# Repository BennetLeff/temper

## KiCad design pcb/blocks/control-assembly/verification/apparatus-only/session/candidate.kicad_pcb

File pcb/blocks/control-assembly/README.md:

# Control-assembly target context (P3 U1)

Authoritative working context for buck/MCU composition. The production board
(`pcb/temper.kicad_pcb`) is read-only; this directory is the only P3-owned
target description.

## Files

- `target-context.json` — outline, six-layer stackup, domains, reserved
  regions, replacement ledger, provenance digests. R1.
- `interfaces.json` — internal required connections vs future RTD/safety/
  programming obligations. Future endpoints are obligations, not connectors.

## Key facts (measured, not inherited)

- Outline 164x234 mm: rect (8,20)-(172,254), Edge.Cuts gr_poly.
- Six copper layers, physical order F.Cu / In3.Cu / In1.Cu / In2.Cu / In4.Cu /
  B.Cu (outer 0.07 mm, inner 0.035 mm; 1.6 mm total; ENIG). Ordinal IDs
  (0/3/1/2/4/31) are not physical order.
- Buck prototype is two-layer 50x40 mm with J1/J2/TP1-TP4/H1-H4 fixtures.
  Only the functional nine transfer:
  U3 (LMR51430), L2 (5.6 uH SRP1265A), C9 (10 uF in), C10 (100 nF boot),
  C11/C12 (2x22 uF out), C13 (100 nF HF), R16 (100 k), R17 (22.1 k).
- MCU source is ten components: module + c_vcc1/c_vcc2 + r_en/c_en +
  r_boot + btn_reset/btn_boot + 2x I2C pullups.
- Existing placeholders: U27 (ESP32-S3-WROOM-1 at 33.1,47.96 rot 90),
  U3 (117.93,149.08), L2 (135.29,147.93). Reserved envelopes:
  MCU 18-52 x 28-68, antenna keepout 18-52 x 20-32, buck 100-146 x 132-162.

## For P1

Definite outline, stackup, allowed regions, and interface obligations are in
the two JSON files. Every input carries a source path and sha256 in
`target-context.json/provenance`. Pending P1 inputs (combined source
wrapper/export, accepted `pcb/blocks/mcu/` geometry) are listed under
`pending_inputs`; U1 does not block on them.

## Verification

Artifact extraction is native KiCad file parse; no new rotation or
net-identity policy was added. Do not add tests that mirror this table —
checks must extract from KiCad and compare against these JSONs.

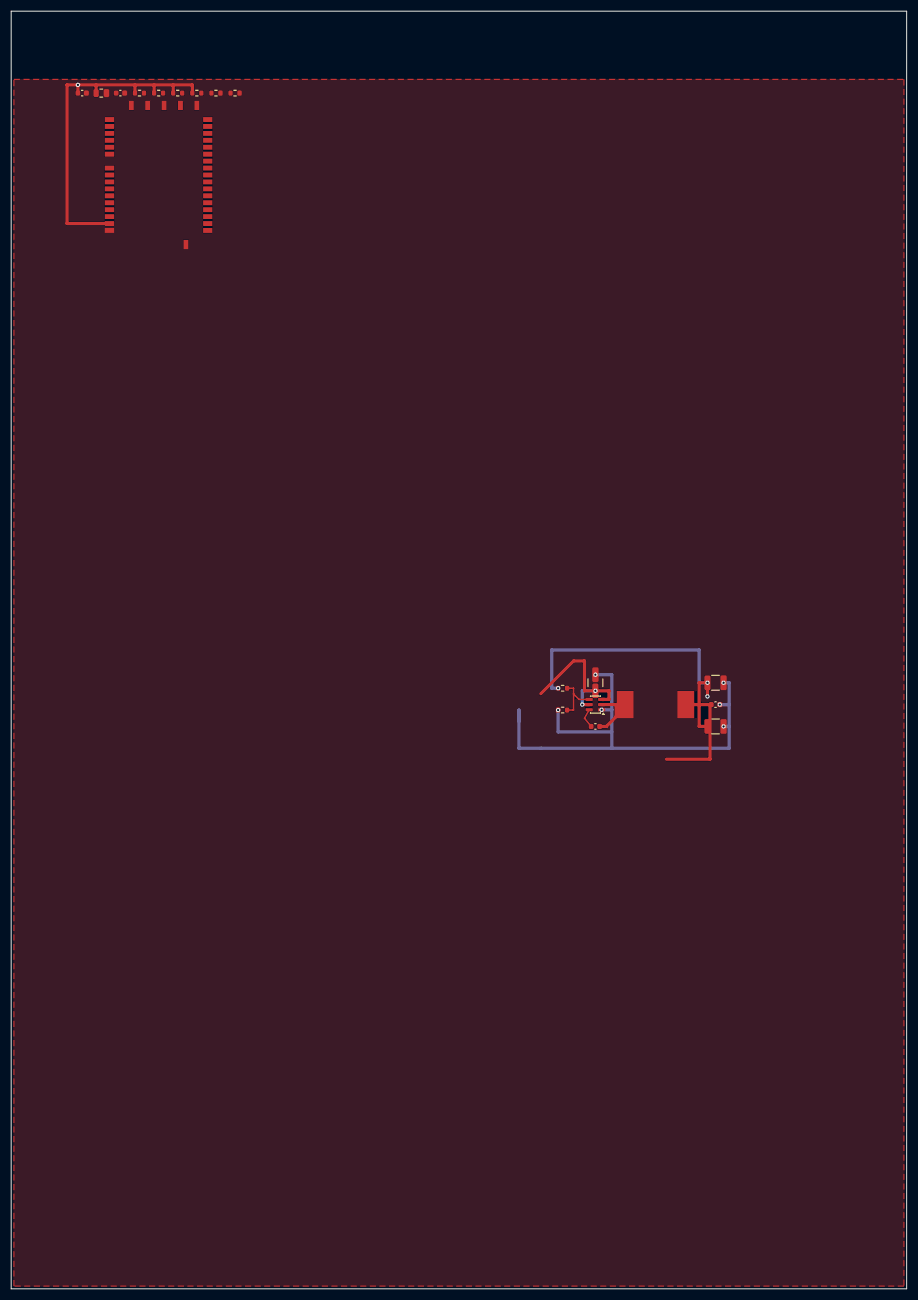
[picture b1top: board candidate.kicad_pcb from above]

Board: 6 copper layers, 164.0 x 234.0 mm, 19 parts (0 on the bottom side), 10 nets.

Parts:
C1, C3, C4: ?; C_1210_3225Metric
C2, C5, C6, C8: ?; C_0603_1608Metric
C7: ?; C_0805_2012Metric
L1: ?; L_Bourns_SRP1265A
R1, R2, R3, R4, R5, R6: ?; R_0603_1608Metric
SW1, SW2: ?; R_0603_1608Metric
U1: ?; SOT-23-6
U2: ?; ESP32-S3-WROOM-1

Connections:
boot: C2.1, U1.6
buck-vcc: C1.1, U1.3, U1.5
buck-vcc-1: C3.1, C4.1, C5.1, C6.1, C7.1, L1.2, R1.1, R3.1, R4.1, R5.1, R6.1, U2.2
en: C8.1, R3.2, SW1.1, U2.3
fb: R1.2, R2.1, U1.4
gnd: C1.2, C3.2, C4.2, C5.2, C6.2, C7.2, C8.2, R2.2, SW1.2, SW2.2, U1.1, U2.1
io0: R4.2, SW2.1, U2.27
scl: R6.2, U2.32
sda: R5.2, U2.31
sw: C2.2, L1.1, U1.2

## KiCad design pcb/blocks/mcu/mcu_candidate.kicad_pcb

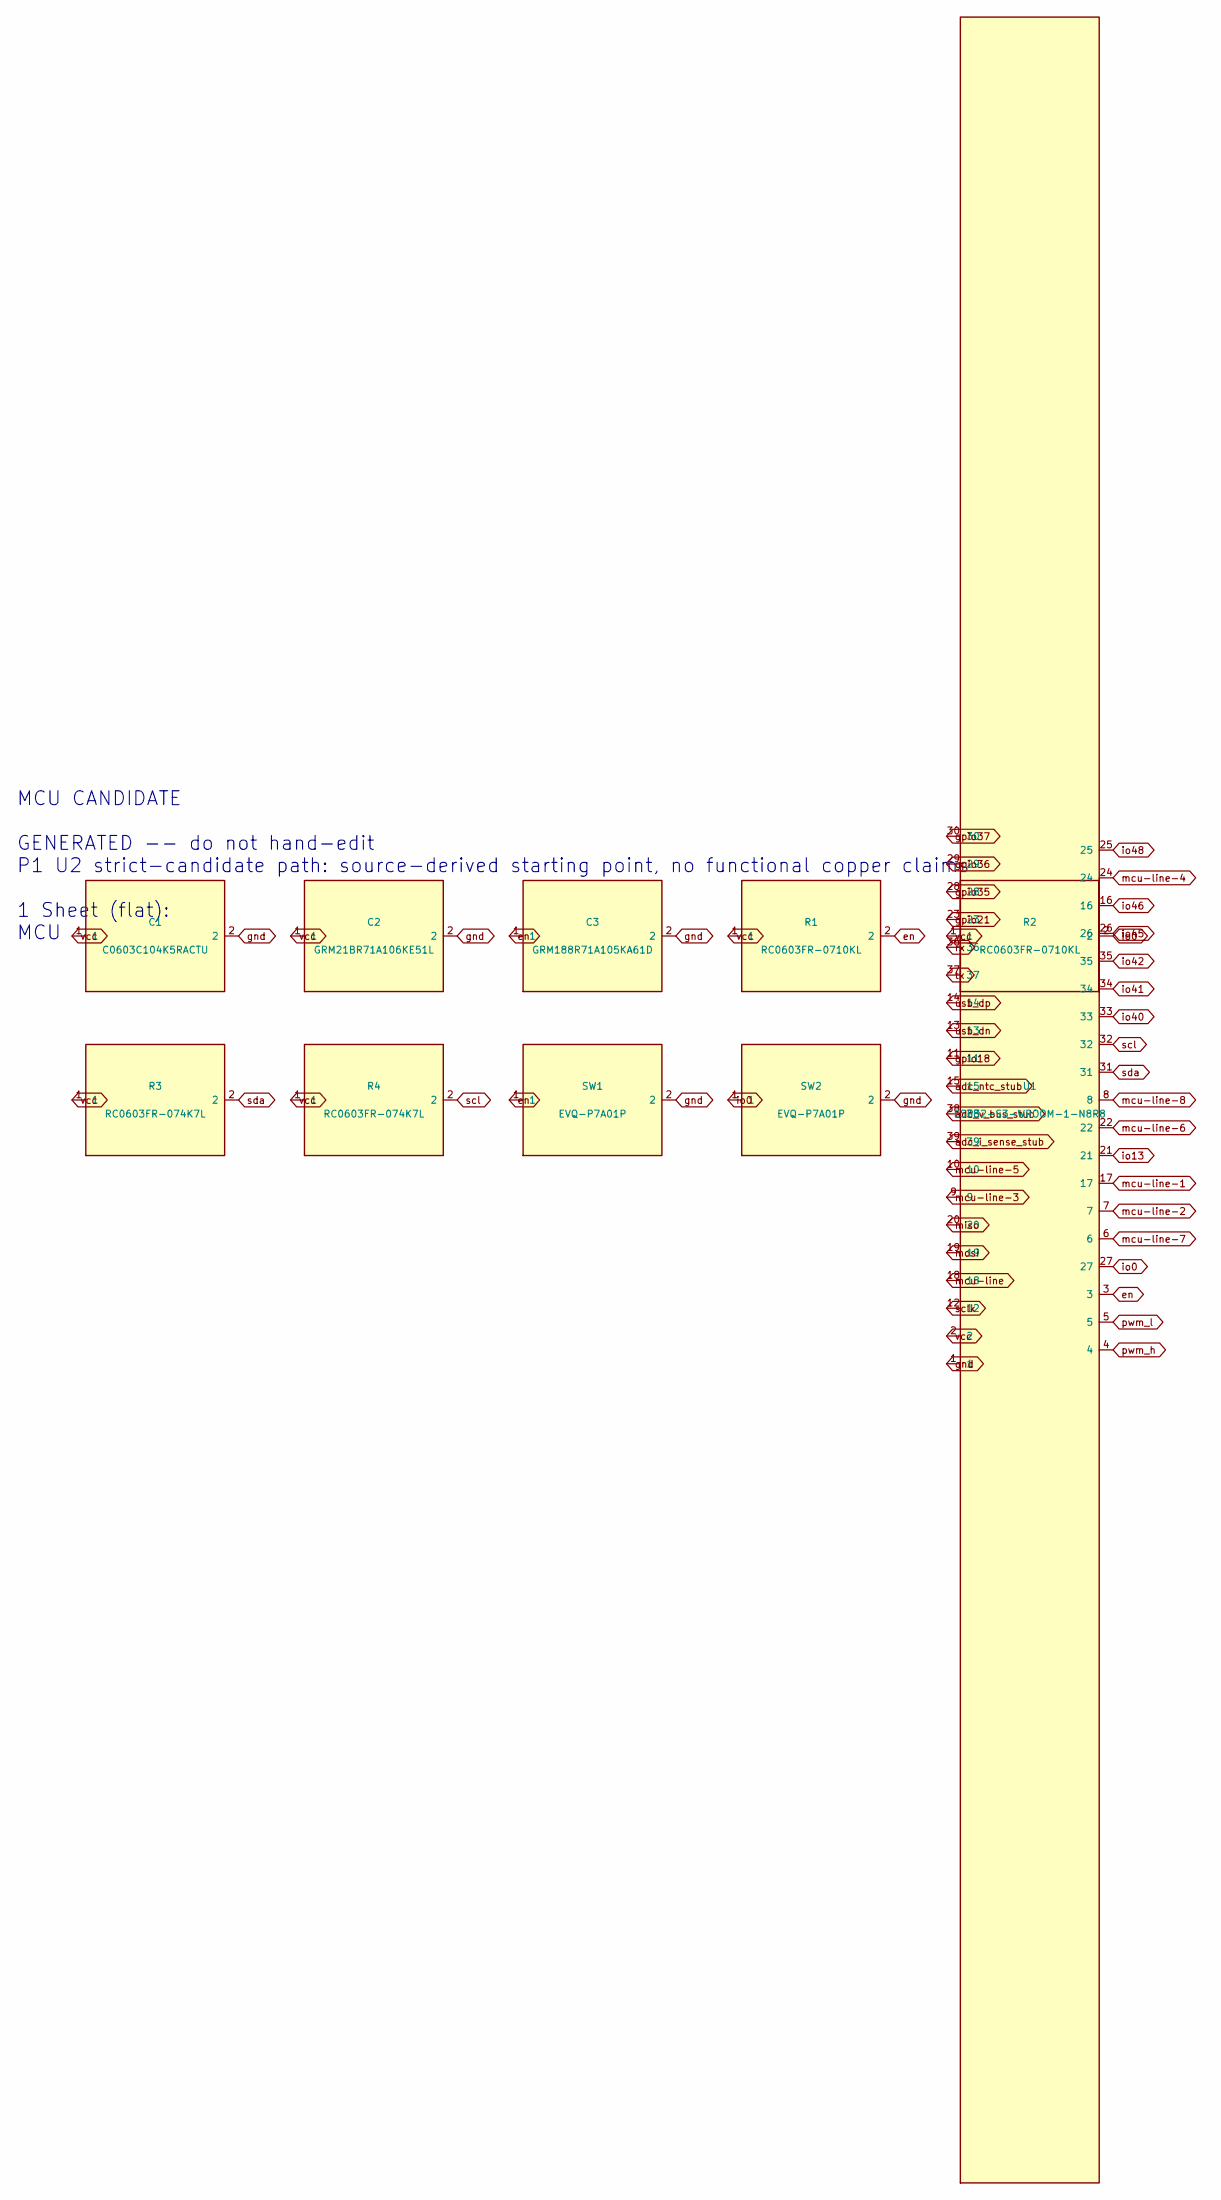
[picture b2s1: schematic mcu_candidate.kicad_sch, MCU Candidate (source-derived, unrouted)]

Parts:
C1: C0603C104K5RACTU; C_0603_1608Metric
C2: GRM21BR71A106KE51L; C_0805_2012Metric
C3: GRM188R71A105KA61D; C_0603_1608Metric
R1, R2: RC0603FR-0710KL; R_0603_1608Metric
R3, R4: RC0603FR-074K7L; R_0603_1608Metric
SW1, SW2: EVQ-P7A01P; SW_SPST_EVQP7A
U1: ESP32-S3-WROOM-1-N8R8; ESP32-S3-WROOM-1

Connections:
adc_i_sense_stub: U1.39
adc_ntc_stub: U1.15
adc_v_bus_stub: U1.38
en: C3.1, R1.2, SW1.1, U1.3
gnd: C1.2, C2.2, C3.2, SW1.2, SW2.2, U1.1
gpio18: U1.11
gpio21: U1.23
gpio35: U1.28
gpio36: U1.29
gpio37: U1.30
io0: R2.2, SW2.1, U1.27
io13: U1.21
io40: U1.33
io41: U1.34
io42: U1.35
io45: U1.26
io46: U1.16
io48: U1.25
mcu-line: U1.18
mcu-line-1: U1.17
mcu-line-2: U1.7
mcu-line-3: U1.9
mcu-line-4: U1.24
mcu-line-5: U1.10
mcu-line-6: U1.22
mcu-line-7: U1.6
mcu-line-8: U1.8
miso: U1.20
mosi: U1.19
pwm_h: U1.4
pwm_l: U1.5
rx: U1.36
scl: R4.2, U1.32
sclk: U1.12
sda: R3.2, U1.31
tx: U1.37
usb_dn: U1.13
usb_dp: U1.14
vcc: C1.1, C2.1, R1.1, R2.1, R3.1, R4.1, U1.2

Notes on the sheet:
MCU CANDIDATE GENERATED -- do not hand-edit P1 U2 strict-candidate path: source-derived starting point, no functional copper claims 1 Sheet (flat): MCU

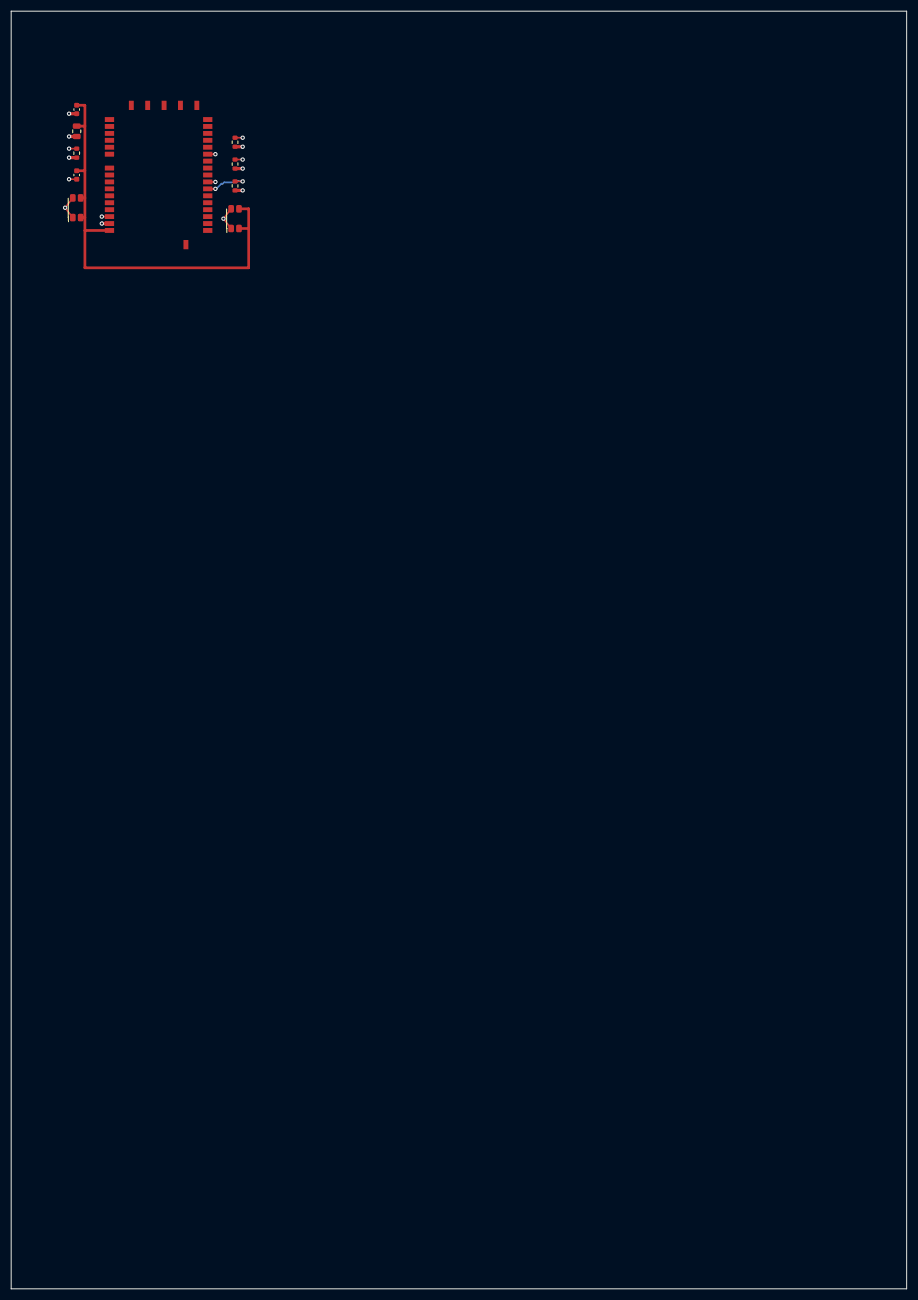
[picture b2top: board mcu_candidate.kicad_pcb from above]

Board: 6 copper layers, 164.0 x 234.0 mm, 10 parts (0 on the bottom side), 6 nets.

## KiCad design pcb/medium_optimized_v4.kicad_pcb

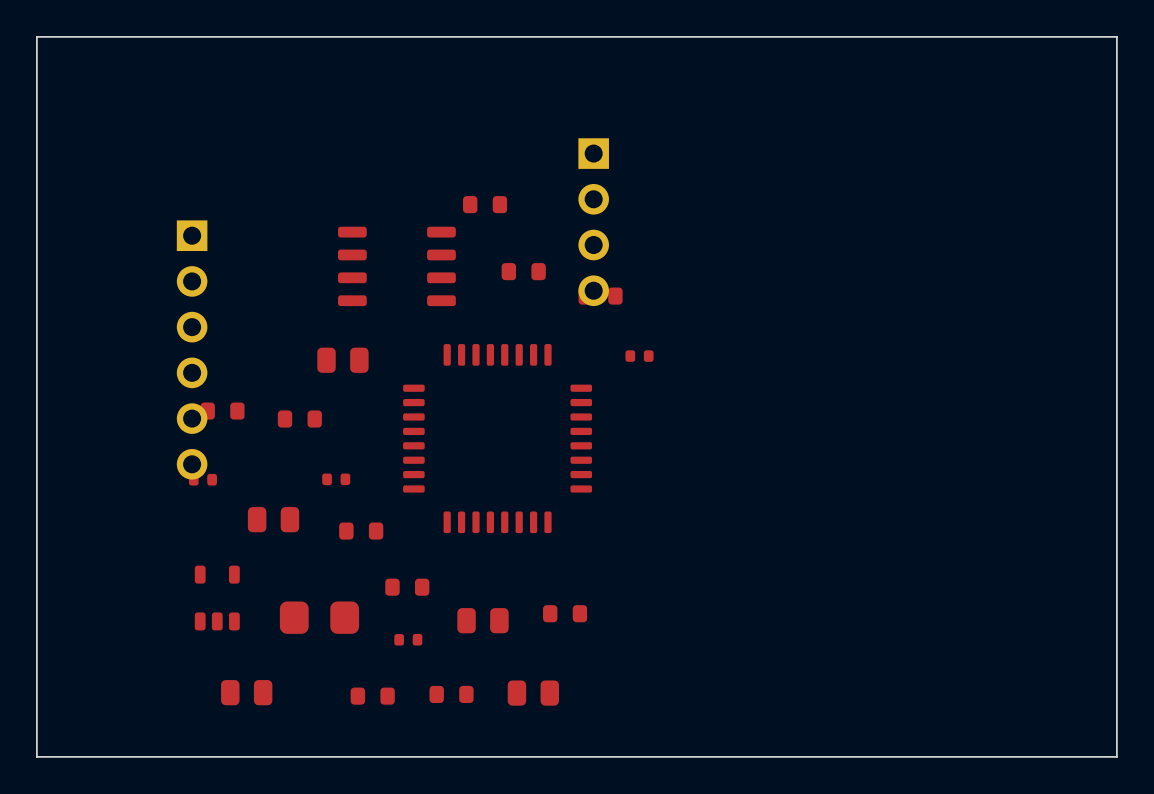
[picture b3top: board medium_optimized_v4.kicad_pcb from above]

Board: 2 copper layers, 60.0 x 40.0 mm, 25 parts (0 on the bottom side), 18 nets, no tracks yet.

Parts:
C1, C2: 100nF; C_0603_1608Metric
C3: 10nF; C_0603_1608Metric
C4: 1uF; C_0603_1608Metric
C5, C6: 10uF; C_0805_2012Metric
C7, C8: 100pF; C_0402_1005Metric
J1: PROG; PinHeader_1x06_P2.54mm_Vertical
J2: I2C; PinHeader_1x04_P2.54mm_Vertical
L1: 10uH; L_0805_2012Metric
L2: 4.7uH; L_1206_3216Metric
R1, R2: 10k; R_0603_1608Metric
R3, R4: 4.7k; R_0603_1608Metric
R5, R6: 1k; R_0603_1608Metric
R7, R8: 100; R_0805_2012Metric
R9, R10: 100k; R_0402_1005Metric
U1: LM358; SOIC-8_3.9x4.9mm_P1.27mm
U2: AMS1117-3.3; SOT-23-5
U3: ATmega328P; TQFP-32_7x7mm_P0.8mm

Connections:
GND: C1.2, C2.2, C3.2, C4.2, C5.2, C6.2, C7.2, C8.2, J1.2, J2.2, R8.2, U1.4, U2.2, U2.3, U3.6, U3.16, U3.22, U3.27, U3.32
I2C_SCL: J2.4, R2.2, U3.10
I2C_SDA: J2.3, R1.2, U3.9
PWM1: R5.1, U3.17
PWM2: R6.1, U3.18
SIG_A: R1.1, R9.2, U1.1, U3.11, U3.19, U3.28
SIG_B: R2.1, R10.2, U1.2, U3.12, U3.20, U3.29
SIG_C: R5.2, U1.3, U3.13, U3.23, U3.30
SIG_D: R6.2, U1.5, U1.6, U3.14, U3.24, U3.31
SPI_CLK: C7.1, J1.5, U3.3
SPI_CS: C8.1, J1.6, U3.4
SPI_MISO: J1.4, R4.1, U3.2
SPI_MOSI: J1.3, R3.1, U3.1
UART_RX: R10.1, U3.8
UART_TX: R9.1, U3.7
VBAT: C3.1, L1.2, R7.2, U3.25
VCC: C1.1, C4.1, C5.1, L1.1, L2.2, R7.1, U1.7, U1.8, U2.1, U3.26
VCC_3V3: C2.1, C6.1, J1.1, J2.1, L2.1, R3.2, R4.2, R8.1, U2.4, U2.5, U3.5, U3.15, U3.21

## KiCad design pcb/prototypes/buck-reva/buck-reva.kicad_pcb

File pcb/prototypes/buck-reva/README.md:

# Buck Rev A — standalone 15 V → 3.3 V prototype board

A small, buildable bench board derived from the reviewed `BuckConverter3V3`
core (LMR51430). This directory holds the standalone schematic and PCB, the
local libraries they resolve against, the freeze manifest and the verification
records.

**This is a prototype, not a qualified or production design.** No hardware has
been assembled or measured. See the deferred-qualification list at the end.

## Status

| Item | State |
|---|---|
| Board | **Frozen**, revision A, 2026-09-10 |
| Source-manifest digest | `83b462c4bbce39b1c367fa2e1965e4a937db26d7e301f505736e2aec8f52cd52` |
| Native ERC / DRC | 0 violations / 0 violations, 0 unconnected (KiCad 10.0.6) |
| Schematic ↔ board connectivity | exact match |
| Manufacturing export | release owner; waits on this freeze |
| Bench measurements | **NOT RUN** |

Freeze details: `verification/board-freeze.md`. Upstream identity:
`source-manifest.json`.

## Interface decisions (for release and bring-up owners)

- **J1 (input)** and **J2 (output)** are both Würth Elektronik
  **691253500002** (DigiKey `732-691253500002-ND`): WR-TBL Series 2535,
  2-position, 5.08 mm, **vertical / top wire entry**, rising-cage screw,
  16 A / 300 V UL, 30–12 AWG.
- Pinout: **J1.1 = VIN (`+15V`)**, **J1.2 = GND (`gnd`)**,
  **J2.1 = 3V3 (`+3V3`)**, **J2.2 = GND (`gnd`)**.
- Probe pads: **TP1 = VIN**, **TP2 = GND**, **TP3 = VOUT**, **TP4 = GND**.
  No TP5; SW stays on the U3.2 / L2.1 pads.
- Silk reads `VIN 13.5-16.5V -> 3V3 0.5A`, `ISOLATED DC - NO MAINS`, plus
  per-terminal polarity and reference designators.

## Files

| Path | Owner | Purpose |
|---|---|---|
| `buck-reva.kicad_sch`, `.kicad_pcb`, `.kicad_pro`, `.kicad_dru` | board | Standalone CAD and project rules |
| `buck-reva.kicad_sym`, `sym-lib-table` | board | Local symbols |
| `buck-reva.pretty/`, `fp-lib-table` | board | Local footprints |
| `source-manifest.json` | board | Freeze manifest (input hashes + provenance + interface) |
| `verification/` | board | ERC/DRC reports, netlist, renders, freeze and review docs |
| `procurement/`, `release/`, `export-release.sh` | release | Purchasing and manufacturing package |
| `docs/hardware/buck-reva/` (repo) | bring-up | Operator runbook and templates |

## Regenerating the derived outputs

All artifacts were produced with **KiCad CLI 10.0.6** at
`/Volumes/KiCad/KiCad/KiCad.app/Contents/MacOS/kicad-cli`:

```sh
K=/Volumes/KiCad/KiCad/KiCad.app/Contents/MacOS/kicad-cli
$K sch erc --format report --severity-all buck-reva.kicad_sch -o release/verification/erc-report.txt
$K sch export netlist --format kicadsexpr buck-reva.kicad_sch -o release/verification/schematic-netlist.kicadsexpr
$K pcb drc --all-track-errors --schematic-parity --severity-all --format report -o release/verification/drc-report.txt buck-reva.kicad_pcb
```

The board was derived once from the reviewed witness fixture; see
`verification/connectivity.md` for the source-to-board reconciliation. Core
footprint UUIDs, positions and pad nets are carried over unchanged.

## Design rules

- 0.2 mm minimum track, 0.2 mm minimum clearance (Default netclass and the
  `buck-reva.kicad_dru` rule), 0.5 mm copper-to-edge (KiCad default, stricter
  than the 0.2 mm starting rule).
- Two layers, 50 × 40 mm, 1.6 mm FR-4, 1 oz copper, lead-free HASL,
  solder mask both sides, front silkscreen only, top-side assembly.

## Deferred (not blockers for this prototype)

Combined capacitor derating, hot-inductor/fault characterization, validated
junction-temperature estimation, behavioral-model correlation and
environmental qualification. Physical assembly and powered bring-up are a
later milestone.

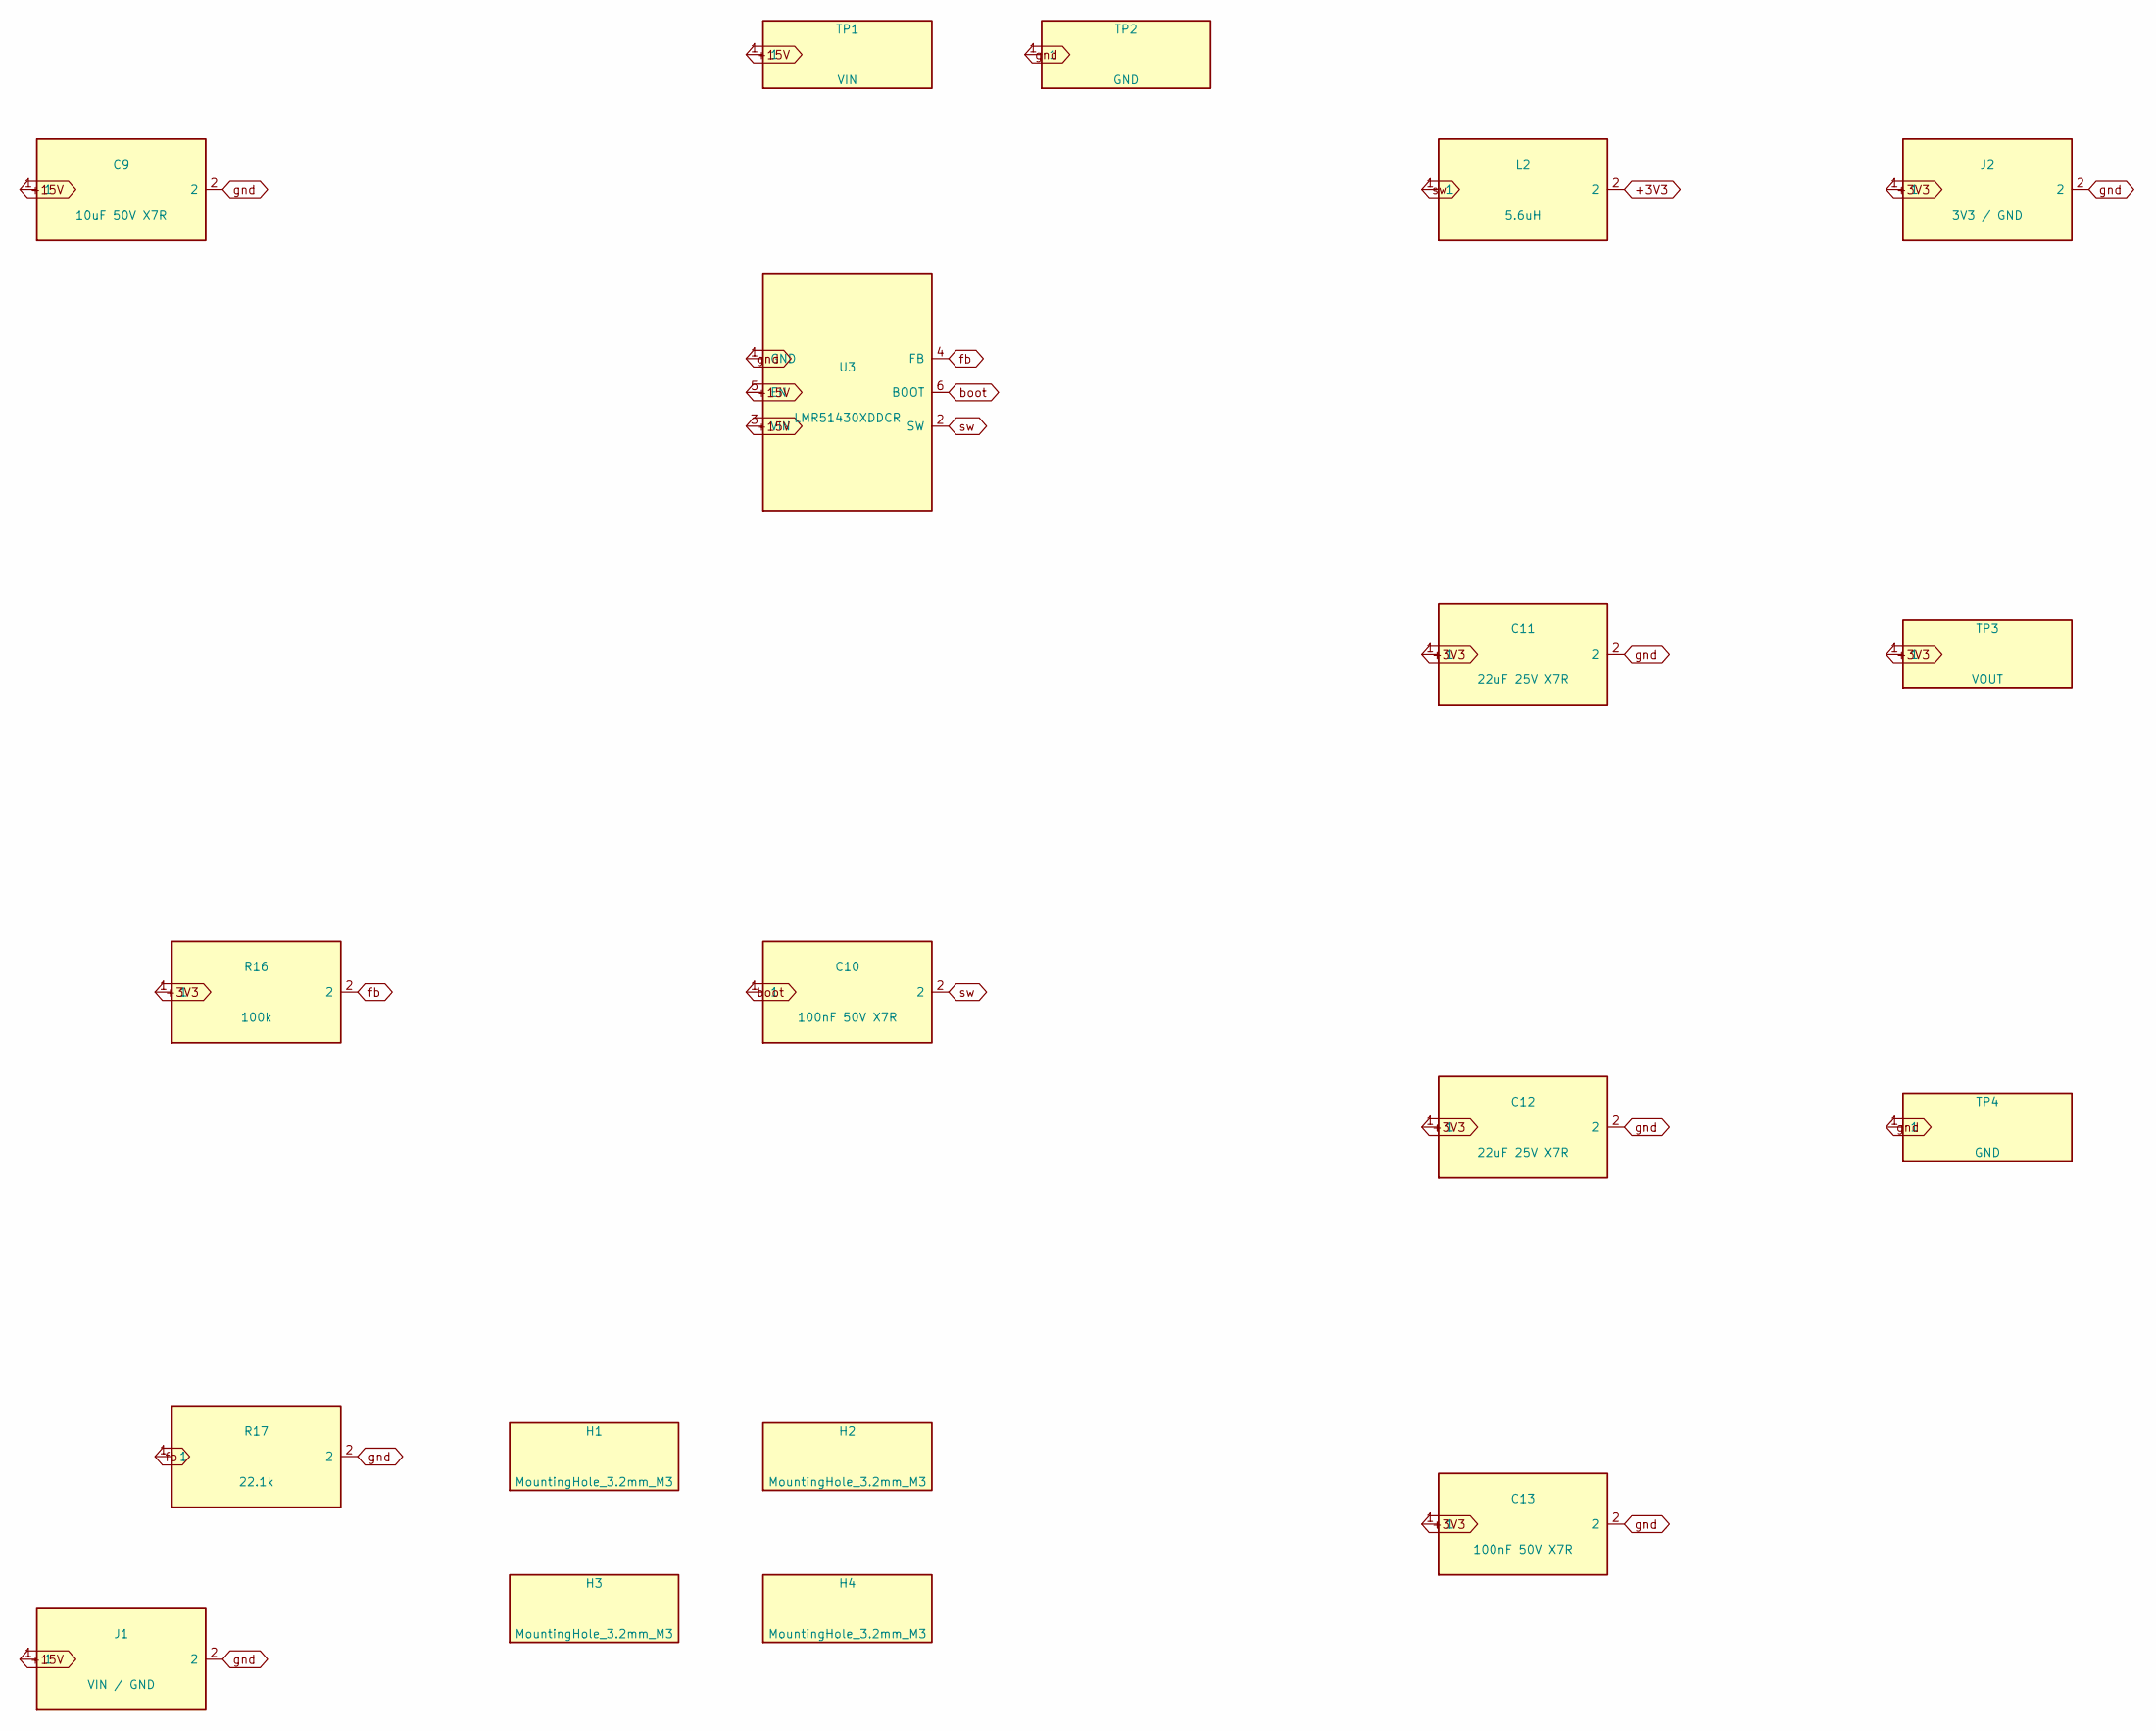
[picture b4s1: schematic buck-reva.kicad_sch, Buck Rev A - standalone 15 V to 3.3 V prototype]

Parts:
C9: 10uF 50V X7R; C_1210_3225Metric; MPN CL32B106KBJZW6E
C10, C13: 100nF 50V X7R; C_0603_1608Metric; MPN C0603C104K5RACTU
C11, C12: 22uF 25V X7R; C_1210_3225Metric; MPN CL32B226KAJNNWE
H1, H2, H3, H4: MountingHole_3.2mm_M3; MPN N/A
J1: VIN / GND; TerminalBlock_5.08mm_1x02; MPN 691253500002
J2: 3V3 / GND; TerminalBlock_5.08mm_1x02; MPN 691253500002
L2: 5.6uH; L_Bourns_SRP1265A; MPN SRP1265A-5R6M
R16: 100k; R_0603_1608Metric; MPN RC0603FR-07100KL
R17: 22.1k; R_0603_1608Metric; MPN RC0603FR-0722K1L
TP1: VIN; TestPoint_Probe_2mm; MPN N/A
TP2, TP4: GND; TestPoint_Probe_2mm; MPN N/A
TP3: VOUT; TestPoint_Probe_2mm; MPN N/A
U3: LMR51430XDDCR; SOT-23-6; MPN LMR51430XDDCR

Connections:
+3V3: C11.1, C12.1, C13.1, J2.1, L2.2, R16.1, TP3.1
+15V: C9.1, J1.1, TP1.1, U3.3 (VIN), U3.5 (EN)
boot: C10.1, U3.6 (BOOT)
fb: R16.2, R17.1, U3.4 (FB)
gnd: C9.2, C11.2, C12.2, C13.2, J1.2, J2.2, R17.2, TP2.1, TP4.1, U3.1 (GND)
sw: C10.2, L2.1, U3.2 (SW)

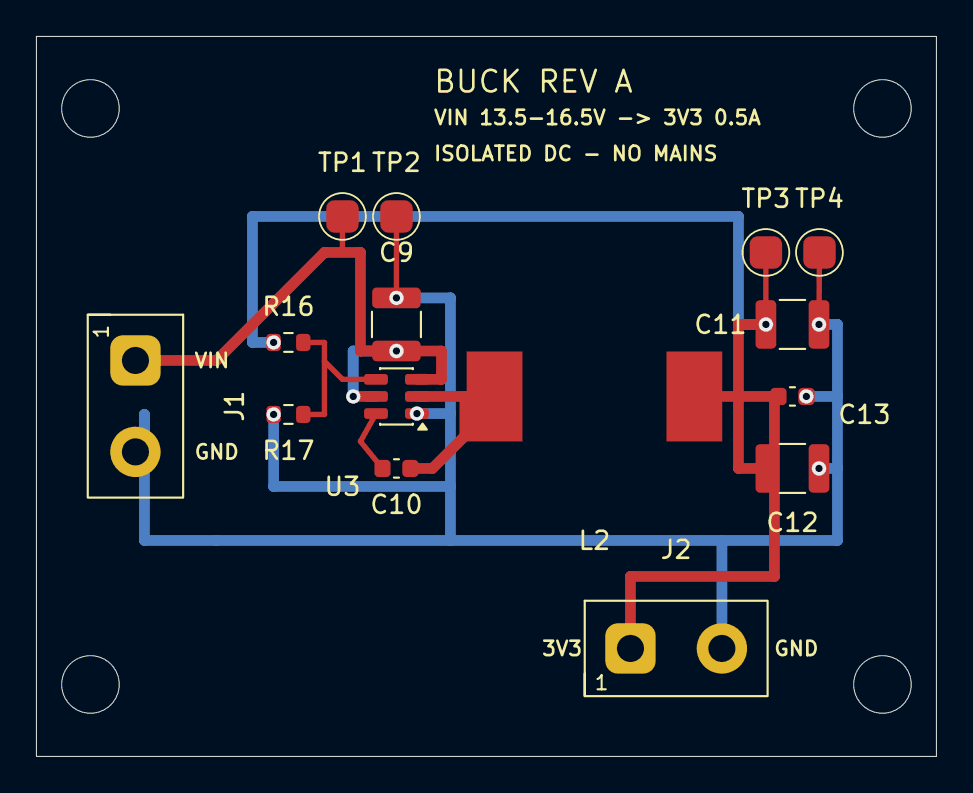
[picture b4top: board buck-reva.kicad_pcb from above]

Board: 2 copper layers, 50.0 x 40.0 mm, 19 parts (0 on the bottom side), 6 nets.

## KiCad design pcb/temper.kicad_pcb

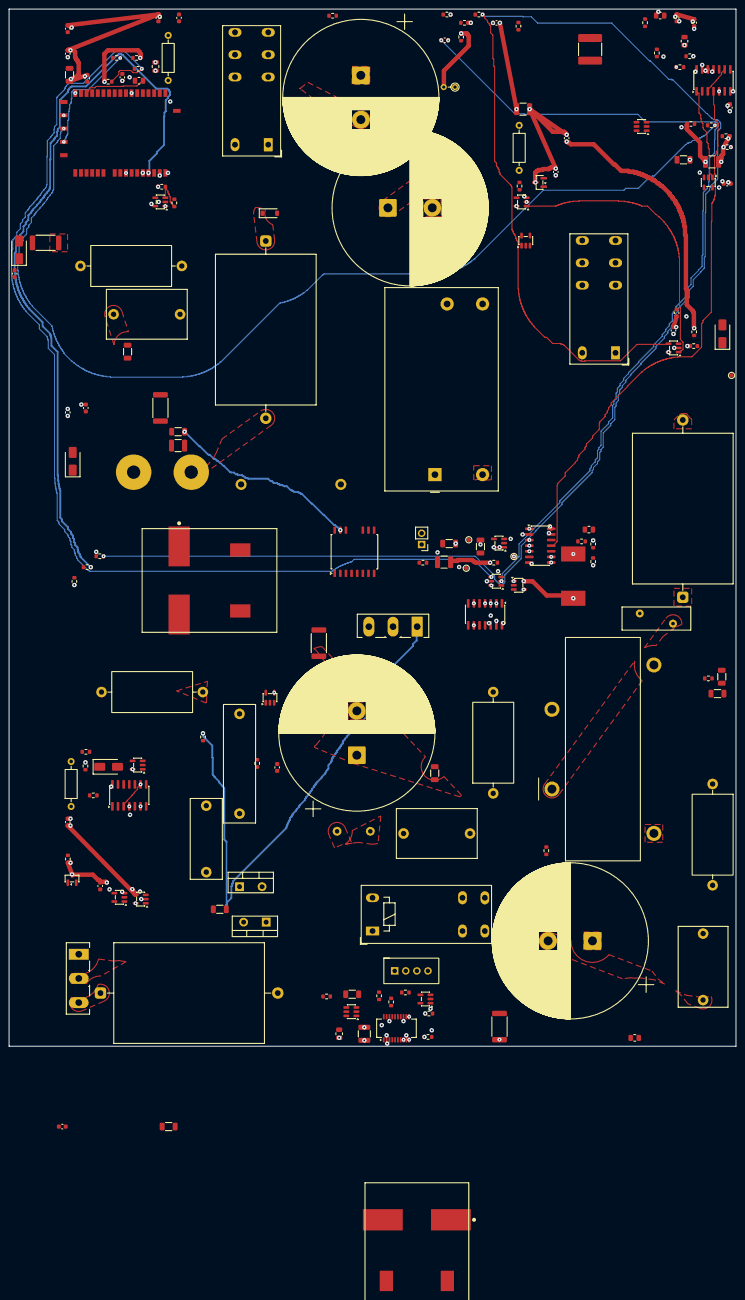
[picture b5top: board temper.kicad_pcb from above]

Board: 6 copper layers, 164.0 x 234.0 mm, 168 parts (0 on the bottom side), 110 nets.

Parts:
C1: ?; C_Rect_L18.0mm_W7.0mm_P15.00mm_FKS3_FKP3
C2, C3, C4, C5: ?; CP_Radial_D35.0mm_P10.00mm_SnapIn
C6: ?; C_Rect_L26.5mm_W7.0mm_P22.50mm_MKS4
C7, C8, C24: ?; C_Rect_L18.0mm_W11.0mm_P15.00mm_FKS3_FKP3
C9, C11, C12, C15, C17: ?; C_1210_3225Metric
C10, C13, C16, C18, C19, C20, C21, C22, C23, C28, C29, C30, C31, C32, C33, C34, C35, C36, C37, C38, C39, C41: ?; C_0603_1608Metric
C14: ?; C_2220_5750Metric
C25, C26, C27: ?; C_Axial_L34.0mm_D22.5mm_P40.00mm_Horizontal
C40: ?; C_0805_2012Metric
D1, D2, D3: ?; D_SMA
D4: ?; D_SOD-123
F1: ?; Fuse_Holder_5x20mm
J1: ?; JST_XH_B4B-XH-A_1x04_P2.50mm_Vertical
J2: ?; PinHeader_1x02_P2.54mm_Vertical
K1: ?; Relay_SPST_Schrack-RT33K012
K2, K3: ?; Relay_SPDT_Schrack-RT314012
L1: ?; CMC_B82726S
L2: ?; L_Bourns_SRP1265A
PS1: ?; Converter_ACDC_MeanWell_IRM-10-xx_THT
Q1, Q2: ?; SOT-23
R1, R60, R75: ?; R_Axial_DIN0207_L6.3mm_D2.5mm_P10.16mm_Horizontal
R2, R3, R12, R13, R28, R40: ?; R_0805_2012Metric
R4, R5, R14, R15: ?; R_2512_6332Metric
R6, R7, R8, R9: ?; R_Axial_DIN0918_L18.0mm_D9.0mm_P22.86mm_Horizontal
R10, R11, R18, R22, R25, R46, R47, R48, R51, R52, R53, R65: ?; R_1206_3216Metric
R16, R17, R19, R20, R21, R23, R24, R26, R27, R29, R31, R32, R33, R35, R36, R37, R38, R39, R41, R42, R43, R44, R45, R49, R50, R54, R56, R57, R58, R59, R61, R62, R63, R64, R66, R67, R68, R69, R70, R71, R72, R73, R74: ?; R_0603_1608Metric
R30: ?; LitzPad_15A
R34: ?; L_0603_1608Metric
R55: ?; R_Axial_DIN0204_L3.6mm_D1.6mm_P2.54mm_Vertical
RT1: ?; R_Disc_D15.0mm_W7.0mm_P7.5mm
RV1: ?; RV_Disc_D15.5mm_W5.2mm_P7.5mm
SW1, SW2: ?; R_0603_1608Metric
T1, T2: ?; CST3015
TP1, TP2, TP3, TP4: ?; TestPoint_Pad_D1.0mm
U1, U2: ?; TO-220-2_Vertical
U3, U13, U21: ?; SOT-23-6
U4, U5: ?; TO-247-3_Vertical
U6: ?; SOIC16W_Isolated
U7: ?; D_SMA
U8: ?; SSOP-20_3.9x8.7mm_P0.635mm
U9, U10, U11, U12, U14, U15, U16, U17, U18, U19, U20, U22: ?; SOT-23-5
U23, U24, U25, U26: ?; SOIC-14_3.9x8.7mm_P1.27mm
U27: ?; ESP32-S3-WROOM-1

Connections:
+3V3: C11.1, C12.1, C13.1, C20.1, C21.1, C30.1, C34.1, C38.1, C39.1, C40.1, L2.2, R16.1, R26.1, R34.1, R42.1, R43.1, R44.1, R56.1, R57.1, R61.1, R62.1, R66.1, R69.1, R70.1, R71.1, R72.1, R73.1, R74.1, U6.3, U6.8, U9.3, U9.4, U13.5, U15.5, U16.5, U17.5, U18.5, U19.5, U20.3, U20.5, U21.5, U22.2, U22.5, U23.14, U24.14, U25.14, U26.2, U26.13, U26.14, U27.2
+15V: C9.1, C15.1, C16.1, PS1.3, R1.1, R10.1, R11.1, R75.1, U3.3, U3.5
+15V_LS: C23.1, U6.11, U7.2
+170V_BUS: C2.1, C4.1, C14.1, C24.1, PS1.1, R4.1, R6.1, R46.1, R51.1, U1.1, U4.2
DC_BUS_RTN: C3.2, C5.2, C8.2, K3.1, R5.2, T2.2, U2.2
DISCHARGE_CTRL: R12.1, U27.24
GATE_HS: R18.1, U6.15
GATE_LS: R22.2, R23.1, U5.1
I_SENSE: C28.1, R25.1, R26.2, R27.1, T1.3, U15.3, U27.39
OCP2_VREF_2V5: U9.5, U16.4, U19.4
PWM_HS: R20.1, U27.4
PWM_LS: R21.1, U27.5
PWR_RTN: C2.2, C3.1, C4.2, C5.1, C6.1, C7.2, C14.2, K2.1, L1.3, PS1.2, R4.2, R5.1, R8.1, T1.2
RELAY_CTRL: R2.1, U27.9
RTD_CS_N: R32.1, U27.18
RTD_DRDY: U8.1, U27.17
RTD_HW_FAULT: R43.2, U14.4, U24.2
RTD_SCK: R29.1, U27.12
RTD_SDI: R31.1, U27.19
RTD_SDO: R33.2, U27.20
SHUTDOWN: TP1.1, TP2.1, U6.5, U26.6, U26.10, U27.10
SW_NODE: C25.1, C26.1, C27.1, D4.1, R19.2, U4.3, U5.2
V_BUS_SENSE: C36.1, R53.2, R54.1, U27.38
WDT_KICK: U20.4, U27.7
WDT_RESET_N: U20.2, U26.12, U27.6
ac_n: C1.2, L1.2, RV1.2
bias: R28.1, U8.4, U8.5
boot: C10.1, U3.6
cs_n: R32.2, U8.16
discharge.k_dis1-coil1: D2.1, K2.2, R10.2
discharge.k_dis1-coil2: D2.2, D3.2, K2.5, K3.5, Q2.1
discharge.k_dis1-nc: K2.4, R7.2, R14.1
discharge.k_dis2-coil1: D3.1, K3.2, R11.2
discharge.k_dis2-nc: K3.4, R9.2, R15.1
discharge.q_dis_drv-g: Q2.2, R12.2, R13.1
discharge.r_dis1a-p2: R6.2, R7.1
discharge.r_dis2a-p2: R8.2, R9.1
discharge.r_snub1-p2: C7.1, R14.2
discharge.r_snub2-p2: C8.1, R15.2
en: C41.1, R71.2, SW1.1, U27.3
fb: R16.2, R17.1, U3.4
gnd: C6.2, C9.2, C11.2, C12.2, C13.2, C15.2, C16.2, C18.2, C19.2, C20.2, C21.2, C28.2, C29.2, C30.2, C31.2, C32.2, C33.2, C34.2, C35.2, C36.2, C37.2, C38.2, C39.2, C40.2, C41.2, J2.2, PS1.4, Q1.3, Q2.3, R3.2, R13.2, R17.2, R24.2, R25.2, R27.2, R36.2, R38.2, R39.2, R41.2, R45.2, R49.2, R54.2, R55.2, R58.2, R60.2, R63.2, R65.2, R67.2, SW1.2, SW2.2, T1.4, T2.4, U3.1, U6.4, U8.9, U8.13, U8.18, U8.19, U9.2, U10.2, U11.2, U12.3, U13.2, U13.4, U14.3, U15.2, U16.2, U17.2, U18.2, U19.2, U20.1, U21.2, U21.4, U22.3, U23.7, U23.11, U23.12, U23.13, U24.5, U24.7, U24.11, U24.12, U24.13, U25.5, U25.7, U25.8, U25.11, U25.12, U25.13, U26.7, U27.1
hb-gnd: C23.2, C24.2, R23.2, T2.1, U5.3, U6.9
hb.gate_hs.driver-p1: R24.1, U6.6
hb.gate_hs.driver-p1-1: C17.1, C22.1, U6.16, U7.1
hb.gate_hs.driver-p2: C17.2, C22.2, D4.2, U6.14
hb.power_loop.q_high-g: R18.2, R19.1, U4.1
i2c_scl_ui: R74.2, U27.32
i2c_sda_ui: R73.2, U27.31
ina: C18.1, R20.2, U6.1
inb: C19.1, R21.2, U6.2
input: R22.1, U6.10
io0: R72.2, SW2.1, U27.27
power_in.bypass_relay-coil1: D1.1, K1.1, R1.2
power_in.bypass_relay-coil2: D1.2, K1.2, Q1.1
power_in.ntc-no: K1.3, RT1.2, U1.2, U2.1
power_in.q_relay_drv-g: Q1.2, R2.2, R3.1
refin_n: R28.2, U8.6, U8.7, U10.3, U11.4
rtd_force_n: J1.4, U8.12
rtd_force_p: J1.1, U8.8
rtd_pan.high_window-out: U11.1, U12.2
rtd_pan.low_window-out: U10.1, U12.1
rtd_pan.r_high_top-inp: R37.2, R38.1, U11.3
rtd_pan.r_low_top-inn: R35.2, R36.1, U10.4
rtd_pan.rail_monitor-ina_p: R40.2, R41.1, U13.3
rtd_pan.rail_monitor-outa: R42.2, U13.1, U14.2
rtd_sense_n: J1.3, U8.11
rtd_sense_p: J1.2, U8.10
s1: C37.1, R65.1, T2.3, U19.3
safety-line: R55.1, R56.2, U17.4, U27.15
safety-line-1: R60.1, R61.2, U18.4
safety-line-2: U24.4, U27.22
safety-line-3: U23.5, U27.8
safety.coil_thermal-line: R64.2, U18.1, U24.8
safety.coil_thermal.comp-inp: R62.2, R63.1, R64.1, U18.3
safety.fault_any_or-a2: U24.3, U24.9, U25.3
safety.fault_any_or-y2: U24.6, U26.9
safety.fault_or3-b2: U25.4, U25.9
safety.fault_or3-y2: U25.6, U26.1
safety.fault_or-a2: U23.3, U23.9
safety.fault_or-b2: U23.4, U26.11
safety.fault_or-y2: U23.6, U24.1
safety.latch-b2: U26.5, U26.8
safety.ocp2-line: TP3.1, U19.1, U25.2
safety.ocp-line: U15.1, U23.1
safety.ocp.comp-inn: R44.2, R45.1, U15.4
safety.ovp-line: R50.2, U16.1, U23.2
safety.ovp.comp-inp: R48.2, R49.1, R50.1, U16.3
safety.ovp.r_adc_top1-p2: R51.2, R52.1
safety.ovp.r_adc_top2-p2: R52.2, R53.1
safety.ovp.r_div_top1-p2: R46.2, R47.1
safety.ovp.r_div_top2-p2: R47.2, R48.1
safety.thermal-line: R59.2, U17.1, U23.8
safety.thermal.comp-inp: R57.2, R58.1, R59.1, U17.3
safety.uvlo_logic-line: R70.2, TP4.1, U22.4, U25.1
safety.uvlo_logic.mon-ina_p: R66.2, R67.1, R68.1, U21.3
safety.uvlo_logic.mon-outa: R68.2, R69.2, U21.1, U22.1
sclk: R29.2, U8.15
sdi: R31.2, U8.14
sdo: R33.1, U8.17
sw: C10.2, L2.1, U3.2
tank-out: R30.2, T1.1
tank.c_tank1-p2: C25.2, C26.2, C27.2, R30.1
thermal.j_fan-p1: J2.1, R75.2
vbias: R35.1, R37.1, U9.1
vcc: C29.1, C31.1, C32.1, C33.1, C35.1, R34.2, R40.1, U8.2, U8.3, U10.5, U11.5, U12.5, U14.5
w1_1: C1.1, F1.2, L1.1, RV1.1
w1_2: K1.4, L1.4, RT1.1
y: R39.1, U12.4, U14.1
y1: U26.3, U26.4

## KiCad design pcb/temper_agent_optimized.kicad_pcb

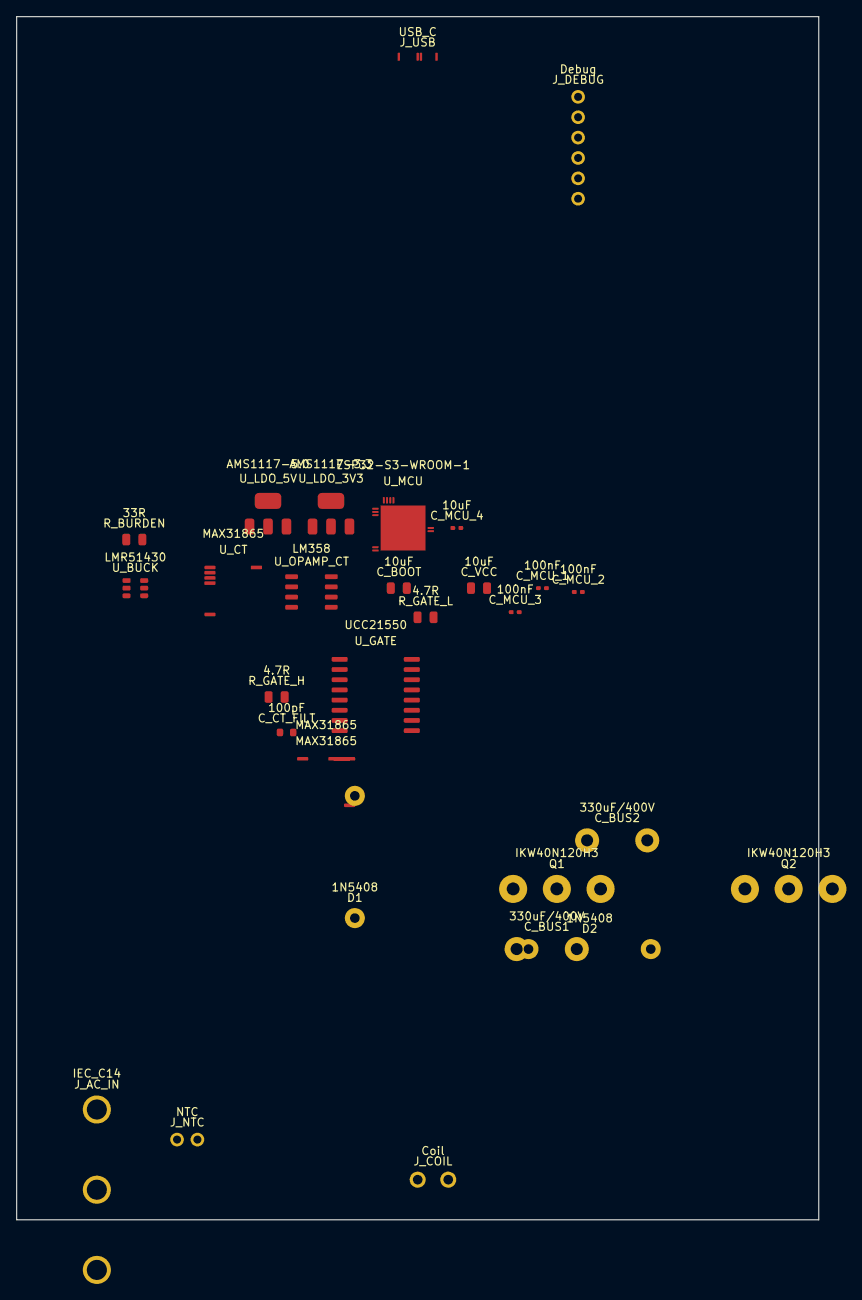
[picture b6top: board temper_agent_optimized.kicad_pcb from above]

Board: 4 copper layers, 100.0 x 150.0 mm, 33 parts (0 on the bottom side), 23 nets, no tracks yet.

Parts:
C_BOOT: 10uF; C_0805_2012Metric
C_BUS1, C_BUS2: 330uF/400V; CP_Radial_D18.0mm_P7.50mm
C_CT_FILT: 100pF; C_0603_1608Metric
C_MCU_1, C_MCU_2, C_MCU_3: 100nF; C_0402_1005Metric
C_MCU_4: 10uF; C_0402_1005Metric
C_VCC: 10uF; C_0805_2012Metric
D1, D2: 1N5408; D_DO-201AD_P15.24mm_Horizontal
J_AC_IN: IEC_C14; IEC_C14_Male
J_COIL: Coil; PhoenixContact_MCV_1,5_2-G-3.81_1x02_P3.81mm_Vertical
J_DEBUG: Debug; PinHeader_1x06_P2.54mm_Vertical
J_NTC: NTC; PinHeader_1x02_P2.54mm_Vertical
J_USB: USB_C; USB_C_Receptacle_HRO_TYPE-C-31-M-12
MAX31865: MAX31865; TSSOP-20_4.4x6.5mm_P0.65mm
MH1, MH2, MH3, MH4: MountingHole_3.2mm_M3
Q1, Q2: IKW40N120H3; TO-247-3_Horizontal_TabDown
R_BURDEN: 33R; R_0805_2012Metric
R_GATE_H: 4.7R; R_0805_2012Metric
R_GATE_L: 4.7R; R_0805_2012Metric
U_BUCK: LMR51430; SOT-23-6
U_CT: MAX31865; TSSOP-20_4.4x6.5mm_P0.65mm
U_GATE: UCC21550; SOIC-16W_7.5x10.3mm_P1.27mm
U_LDO_3V3: AMS1117-3.3; SOT-223-3_TabPin2
U_LDO_5V: AMS1117-5.0; SOT-223-3_TabPin2
U_MCU: ESP32-S3-WROOM-1; QFN-56-1EP_7x7mm_P0.4mm_EP5.6x5.6mm
U_OPAMP_CT: LM358; SOIC-8_3.9x4.9mm_P1.27mm

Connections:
+3V3: C_MCU_1.1, C_MCU_2.1, C_MCU_3.1, C_MCU_4.1, J_DEBUG.2, MAX31865.20, U_CT.20, U_LDO_3V3.2, U_LDO_3V3.4, U_MCU.1
+5V: U_BUCK.2, U_BUCK.4, U_LDO_3V3.3, U_LDO_5V.2, U_LDO_5V.4, U_OPAMP_CT.7, U_OPAMP_CT.8
+15V: C_VCC.1, U_BUCK.3, U_GATE.1, U_GATE.11, U_LDO_5V.3
AC_L: D1.1, J_AC_IN.1
AC_N: D2.2, J_AC_IN.2
CGND: C_VCC.2, U_GATE.5, U_GATE.6, U_GATE.7, U_GATE.8
DC_BUS+: C_BUS1.1, C_BUS2.1, D1.2, Q1.3
GATE_H: Q1.1, R_GATE_H.1, R_GATE_H.2, U_GATE.15
GATE_L: Q2.1, R_GATE_L.1, R_GATE_L.2, U_GATE.10
GND: C_CT_FILT.2, C_MCU_1.2, C_MCU_2.2, C_MCU_3.2, C_MCU_4.2, J_AC_IN.3, J_COIL.2, J_DEBUG.1, J_NTC.2, J_USB.A1, J_USB.A12, MAX31865.10, R_BURDEN.2, U_BUCK.1, U_BUCK.5, U_BUCK.6, U_CT.10, U_LDO_3V3.1, U_LDO_5V.1, U_MCU.2, U_MCU.57, U_OPAMP_CT.4
I_SENSE: C_CT_FILT.1, R_BURDEN.1, U_MCU.15, U_OPAMP_CT.1, U_OPAMP_CT.2, U_OPAMP_CT.3, U_OPAMP_CT.5, U_OPAMP_CT.6
PGND: C_BUS1.2, C_BUS2.2, Q2.2, U_GATE.12, U_GATE.13
PWM_H: U_GATE.2, U_MCU.13
PWM_L: U_GATE.3, U_MCU.14
SPI_CLK: MAX31865.1, U_CT.1, U_MCU.20
SPI_CS_TEMP: U_CT.4, U_MCU.23
SPI_MISO: MAX31865.3, U_CT.3, U_MCU.22
SPI_MOSI: MAX31865.2, U_CT.2, U_MCU.21
SW_NODE: C_BOOT.2, J_COIL.1, Q1.2, Q2.3, U_GATE.9, U_GATE.16
TEMP_SENSE: J_NTC.1, MAX31865.4
USB_D+: J_USB.A6, U_MCU.40
USB_D-: J_USB.B6, U_MCU.41
VCC_BOOT: C_BOOT.1, U_GATE.14
